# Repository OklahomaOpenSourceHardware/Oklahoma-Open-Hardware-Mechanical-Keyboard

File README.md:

# Oklahoma-Open-Hardware-Mechanical-Keyboard
Oklahoma themed open source hardware licensed keyboard from the Oklahoma community

## Layout

http://www.keyboard-layout-editor.com/#/gists/58d102278691380e818329089bf505ac

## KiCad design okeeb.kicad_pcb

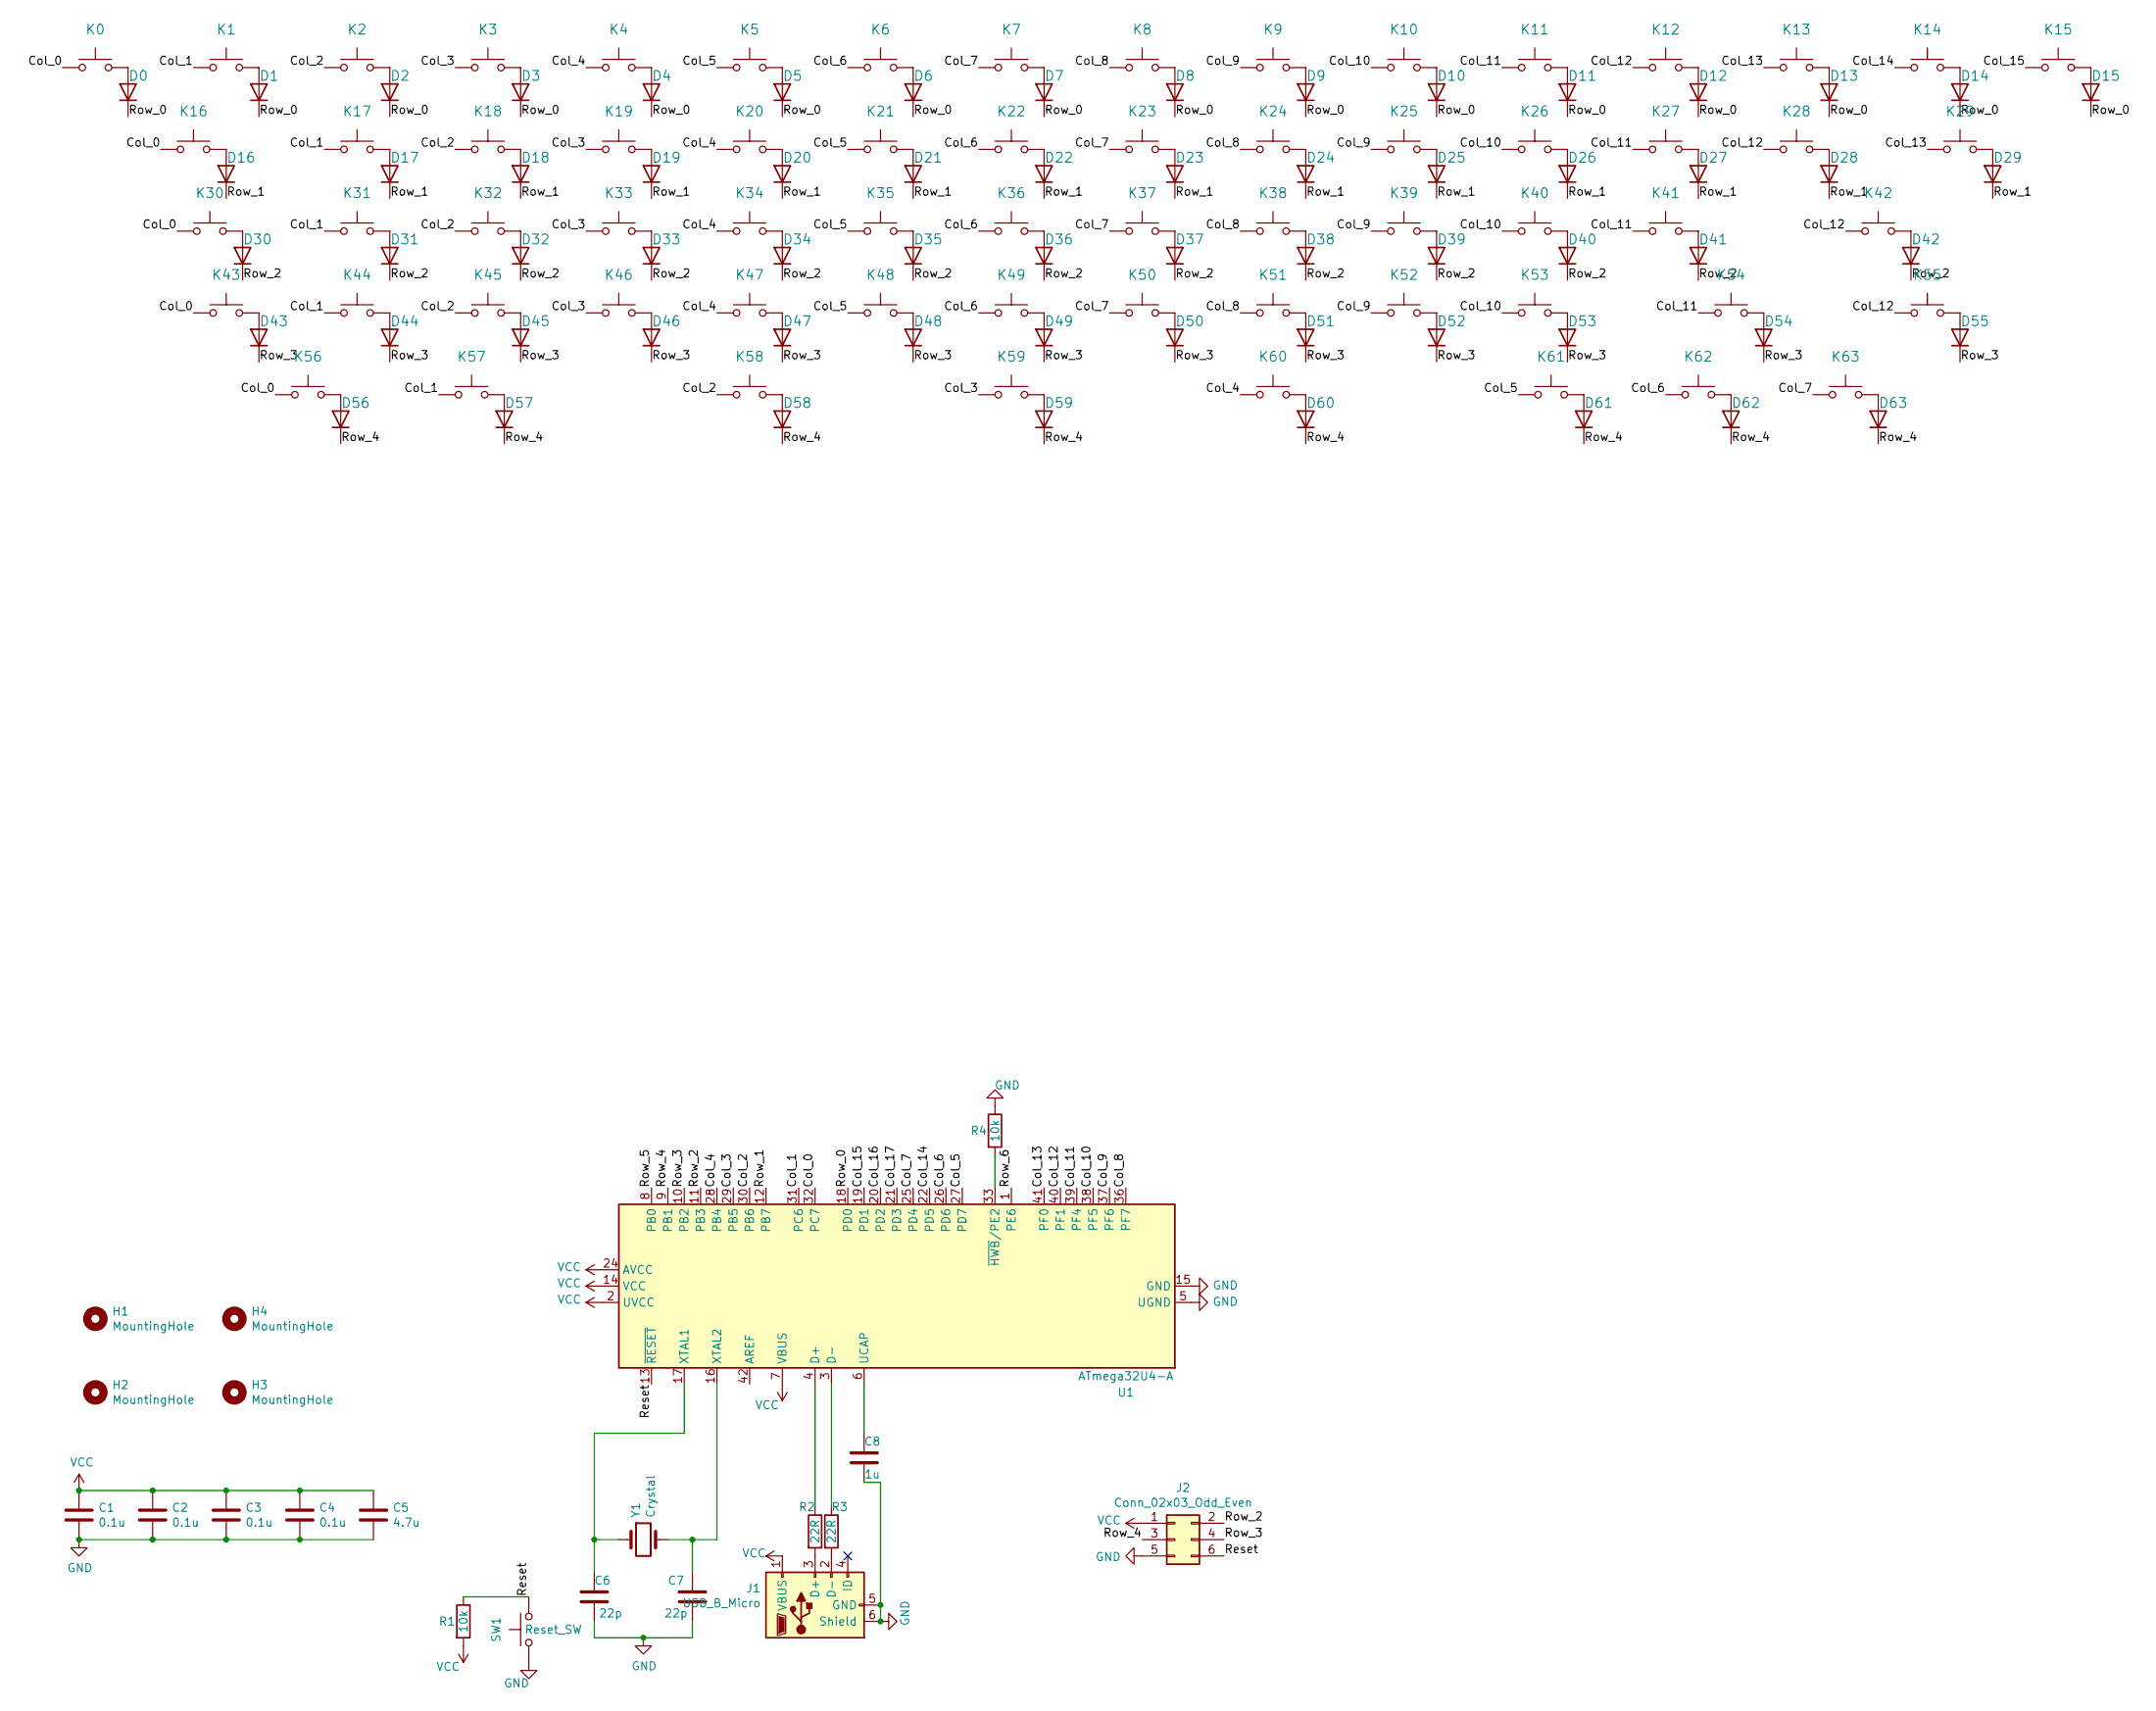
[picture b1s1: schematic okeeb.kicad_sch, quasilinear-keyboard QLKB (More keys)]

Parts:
C1, C2, C3, C4: 0.1u; C_0805_2012Metric_Pad1.15x1.40mm_HandSolder
C5: 4.7u; C_0805_2012Metric_Pad1.15x1.40mm_HandSolder
C6, C7: 22p; C_0805_2012Metric_Pad1.15x1.40mm_HandSolder
C8: 1u; C_0805_2012Metric_Pad1.15x1.40mm_HandSolder
D0, D1, D2, D3, D4, D5, D6, D7, D8, D9, D10, D11, D12, D13, D14, D15, D16, D17, D18, D19, D20, D21, D22, D23, D24, D25, D26, D27, D28, D29, D30, D31, D32, D33, D34, D35, D36, D37, D38, D39, D40, D41, D42, D43, D44, D45, D46, D47, D48, D49, D50, D51, D52, D53, D54, D55, D56, D57, D58, D59, D60, D61, D62, D63: D; D_0805_2012Metric_Pad1.15x1.40mm_HandSolder
H1, H2, H3, H4: MountingHole; MountingHole_3.2mm_M3_DIN965
J1: USB_B_Micro; USB_Micro-B_Wuerth_629105150521_CircularHoles
J2: Conn_02x03_Odd_Even; PinHeader_2x03_P2.54mm_Vertical
K0, K1, K2, K3, K4, K5, K6, K7, K8, K9, K10, K11, K12, K13, K14, K15, K17, K18, K19, K20, K21, K22, K23, K24, K25, K26, K27, K28, K31, K32, K33, K34, K35, K36, K37, K38, K39, K40, K41, K43, K44, K45, K46, K47, K48, K49, K50, K51, K52, K53, K55, K59, K62: KEYSW; SW_Cherry_MX_1.00u_PCB
K16, K29: KEYSW; SW_Cherry_MX_1.50u_PCB
K30, K56, K57, K61, K63: KEYSW; SW_Cherry_MX_1.25u_PCB
K42: KEYSW; SW_Cherry_MX_2.25u_PCB
K54: KEYSW; SW_Cherry_MX_2.00u_PCB
K58, K60: KEYSW; SW_Cherry_MX_2.75u_PCB
R1, R4: 10k; R_0805_2012Metric_Pad1.15x1.40mm_HandSolder
R2, R3: 22R; R_0805_2012Metric_Pad1.15x1.40mm_HandSolder
SW1: Reset_SW; SW_Push_1P1T_NO_6x6mm_H9.5mm
U1: ATmega32U4-A; TQFP-44_10x10mm_P0.8mm
Y1: Crystal; Crystal_SMD_5032-2Pin_5.0x3.2mm_HandSoldering

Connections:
/Col_0: K0.1, K16.1, K30.1, K43.1, K56.1, U1.32 (PC7)
/Col_1: K1.1, K17.1, K31.1, K44.1, K57.1, U1.31 (PC6)
/Col_2: K2.1, K18.1, K32.1, K45.1, K58.1, U1.30 (PB6)
/Col_3: K3.1, K19.1, K33.1, K46.1, K59.1, U1.29 (PB5)
/Col_4: K4.1, K20.1, K34.1, K47.1, K60.1, U1.28 (PB4)
/Col_5: K5.1, K21.1, K35.1, K48.1, K61.1, U1.27 (PD7)
/Col_6: K6.1, K22.1, K36.1, K49.1, K62.1, U1.26 (PD6)
/Col_7: K7.1, K23.1, K37.1, K50.1, K63.1, U1.25 (PD4)
/Col_8: K8.1, K24.1, K38.1, K51.1, U1.36 (PF7)
/Col_9: K9.1, K25.1, K39.1, K52.1, U1.37 (PF6)
/Col_10: K10.1, K26.1, K40.1, K53.1, U1.38 (PF5)
/Col_11: K11.1, K27.1, K41.1, K54.1, U1.39 (PF4)
/Col_12: K12.1, K28.1, K42.1, K55.1, U1.40 (PF1)
/Col_13: K13.1, K29.1, U1.41 (PF0)
/Col_14: K14.1, U1.22 (PD5)
/Col_15: K15.1, U1.19 (PD1)
/Col_16: U1.20 (PD2)
/Col_17: U1.21 (PD3)
/Row_0: D0.1 (K), D1.1 (K), D2.1 (K), D3.1 (K), D4.1 (K), D5.1 (K), D6.1 (K), D7.1 (K), D8.1 (K), D9.1 (K), D10.1 (K), D11.1 (K), D12.1 (K), D13.1 (K), D14.1 (K), D15.1 (K), U1.18 (PD0)
/Row_1: D16.1 (K), D17.1 (K), D18.1 (K), D19.1 (K), D20.1 (K), D21.1 (K), D22.1 (K), D23.1 (K), D24.1 (K), D25.1 (K), D26.1 (K), D27.1 (K), D28.1 (K), D29.1 (K), U1.12 (PB7)
/Row_2: D30.1 (K), D31.1 (K), D32.1 (K), D33.1 (K), D34.1 (K), D35.1 (K), D36.1 (K), D37.1 (K), D38.1 (K), D39.1 (K), D40.1 (K), D41.1 (K), D42.1 (K), J2.2, U1.11 (PB3)
/Row_3: D43.1 (K), D44.1 (K), D45.1 (K), D46.1 (K), D47.1 (K), D48.1 (K), D49.1 (K), D50.1 (K), D51.1 (K), D52.1 (K), D53.1 (K), D54.1 (K), D55.1 (K), J2.4, U1.10 (PB2)
/Row_4: D56.1 (K), D57.1 (K), D58.1 (K), D59.1 (K), D60.1 (K), D61.1 (K), D62.1 (K), D63.1 (K), J2.3, U1.9 (PB1)
/Row_5: U1.8 (PB0)
/Row_6: U1.1 (PE6)
GND: C1.2, C2.2, C3.2, C4.2, C5.2, C6.2, C7.2, C8.2, J1.5 (GND), J1.6 (Shield), J2.5, R4.1, SW1.1, U1.5 (UGND), U1.15 (GND), U1.23 (GND), U1.35 (GND), U1.43 (GND)
unnamed: C6.1, U1.17 (XTAL1), Y1.1
unnamed: C7.1, U1.16 (XTAL2), Y1.2
unnamed: C8.1, U1.6 (UCAP)
unnamed: D0.2 (A), K0.2
unnamed: D1.2 (A), K1.2
unnamed: D2.2 (A), K2.2
unnamed: D3.2 (A), K3.2
unnamed: D4.2 (A), K4.2
unnamed: D5.2 (A), K5.2
unnamed: D6.2 (A), K6.2
unnamed: D7.2 (A), K7.2
unnamed: D8.2 (A), K8.2
unnamed: D9.2 (A), K9.2
unnamed: D10.2 (A), K10.2
unnamed: D11.2 (A), K11.2
unnamed: D12.2 (A), K12.2
unnamed: D13.2 (A), K13.2
unnamed: D14.2 (A), K14.2
unnamed: D15.2 (A), K15.2
unnamed: D16.2 (A), K16.2
unnamed: D17.2 (A), K17.2
unnamed: D18.2 (A), K18.2
unnamed: D19.2 (A), K19.2
unnamed: D20.2 (A), K20.2
unnamed: D21.2 (A), K21.2
unnamed: D22.2 (A), K22.2
unnamed: D23.2 (A), K23.2
unnamed: D24.2 (A), K24.2
unnamed: D25.2 (A), K25.2
unnamed: D26.2 (A), K26.2
unnamed: D27.2 (A), K27.2
unnamed: D28.2 (A), K28.2
unnamed: D29.2 (A), K29.2
unnamed: D30.2 (A), K30.2
unnamed: D31.2 (A), K31.2
unnamed: D32.2 (A), K32.2
unnamed: D33.2 (A), K33.2
unnamed: D34.2 (A), K34.2
unnamed: D35.2 (A), K35.2
unnamed: D36.2 (A), K36.2
unnamed: D37.2 (A), K37.2
unnamed: D38.2 (A), K38.2
unnamed: D39.2 (A), K39.2
unnamed: D40.2 (A), K40.2
unnamed: D41.2 (A), K41.2
unnamed: D42.2 (A), K42.2
unnamed: D43.2 (A), K43.2
unnamed: D44.2 (A), K44.2
unnamed: D45.2 (A), K45.2
unnamed: D46.2 (A), K46.2
unnamed: D47.2 (A), K47.2
unnamed: D48.2 (A), K48.2
unnamed: D49.2 (A), K49.2
unnamed: D50.2 (A), K50.2
unnamed: D51.2 (A), K51.2
unnamed: D52.2 (A), K52.2
unnamed: D53.2 (A), K53.2
unnamed: D54.2 (A), K54.2
unnamed: D55.2 (A), K55.2
unnamed: D56.2 (A), K56.2
unnamed: D57.2 (A), K57.2
unnamed: D58.2 (A), K58.2
unnamed: D59.2 (A), K59.2
unnamed: D60.2 (A), K60.2
unnamed: D61.2 (A), K61.2
unnamed: D62.2 (A), K62.2
unnamed: D63.2 (A), K63.2
unnamed: R2.1, U1.4 (D+)
unnamed: R3.1, U1.3 (D-)
unnamed: R4.2, U1.33 (~HWB/PE2)
VCC: C1.1, C2.1, C3.1, C4.1, C5.1, J1.1 (VBUS), J2.1, R1.2, U1.2 (UVCC), U1.7 (VBUS), U1.14 (VCC), U1.24 (AVCC), U1.34 (VCC), U1.44 (AVCC)

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
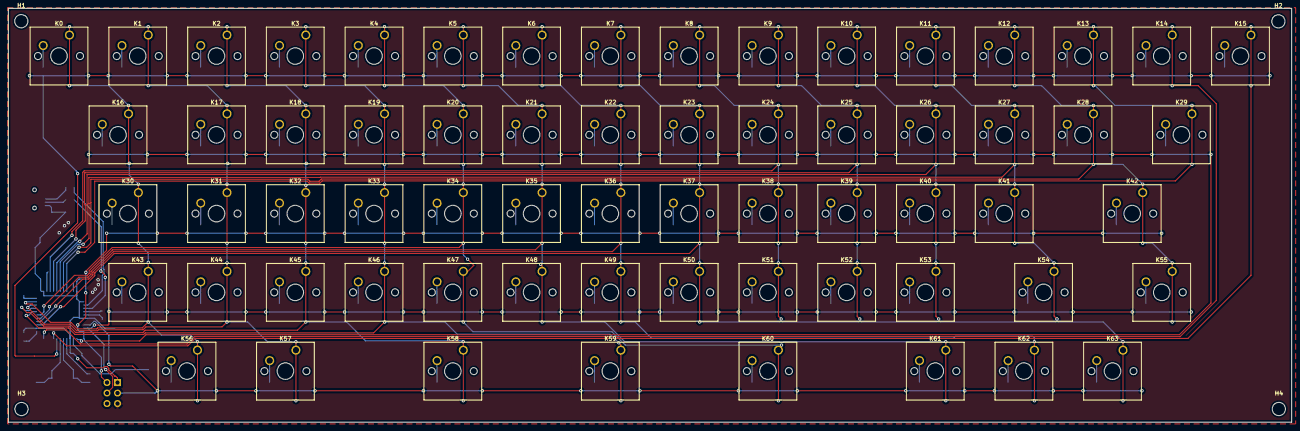
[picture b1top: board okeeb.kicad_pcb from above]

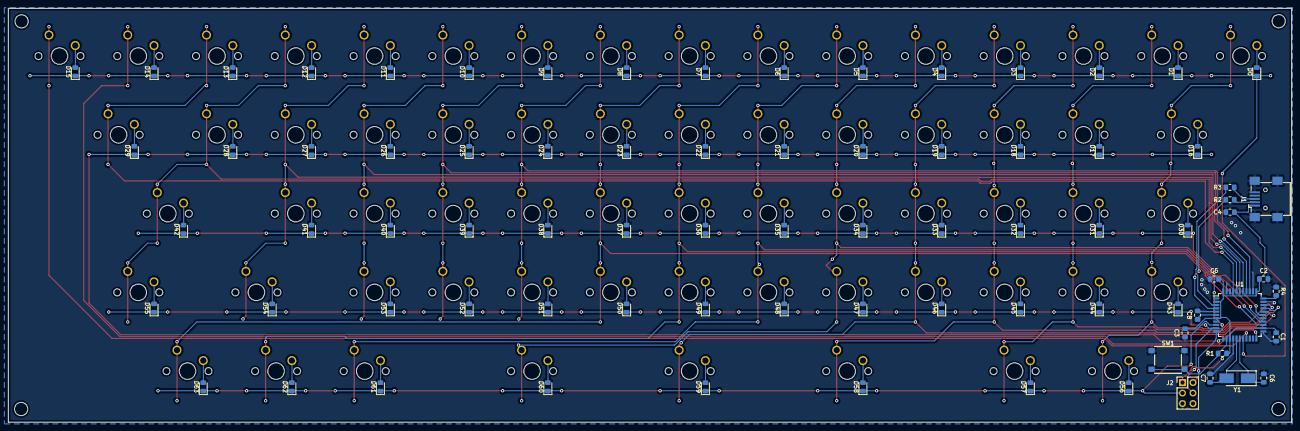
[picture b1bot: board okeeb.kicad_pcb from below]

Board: 2 copper layers, 310.4 x 100.1 mm, 149 parts (81 on the bottom side), 96 nets.

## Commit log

2022-05-25 Initial commit
    Used https://github.com/jeroen94704/klepcbgen to generate initial layout
    Based on this design http://www.keyboard-layout-editor.com/#/gists/58d102278691380e818329089bf505ac
2022-05-25 Update README.md
    Add image and link to layout on the http://www.keyboard-layout-editor.com site.
2022-06-01 Update .gitignore
    adjusted ignore
2022-06-08 added kaailh sockets Signed-off-by: lokimetasmith <lokimail@gmail.com>
2022-06-14 adding initial mechanical stackup
2022-06-14 Create raw layout data.txt
    generated from online keyboard editor
2022-06-14 Add files via upload
    json download of layout
2022-06-14 added mechanical drawings first draft, and list of parts in BOM for mechanical components
2022-06-16 adding in 3D models and changed key 15 so it only has one key as opposed to two
2022-06-29 converting it to ESP32-s3, added LED's, USB-C, IO expanders, and switching power supply
2022-06-29 initial schematic capture
2022-07-09 updated libraries, lots of minor fixes
2022-07-16 added waveshare e-ink display, and battery charger
2022-07-21 Added a sd card, resistor footprints, and a bunch of in process ideas for displays
2022-11-16 cleaned up traces, added in attiny optional io expander,added in rotary dial, settled on e-ink displays. removed smart card password managment, oled, sd card, etc.
2023-02-12 Intermittint upload, lots of changes
